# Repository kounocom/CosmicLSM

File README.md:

# CosmicLSM - An ESP32-C3 based custom SlimeVR PCB

## Notes:

 - Currently untested!
 - Designed for handsoldering, BOM contains parts that are "extended" on JLC, or straight up not present
 - CPL file not tested at all
 - See "Outputs/" for production files
 - IMUs that are compatible :
 - - BMI160
 - - BMI270
 - - BMI323(?)
 - - LSM6DSV
 - - LSM6DSV16X
 - - ICM-40608
 - - Potentially more, but there will be no firmware support, even for some of the ones listed above
 - Special thanks to Gorbit99 and wigwagwent for their help with making this <3

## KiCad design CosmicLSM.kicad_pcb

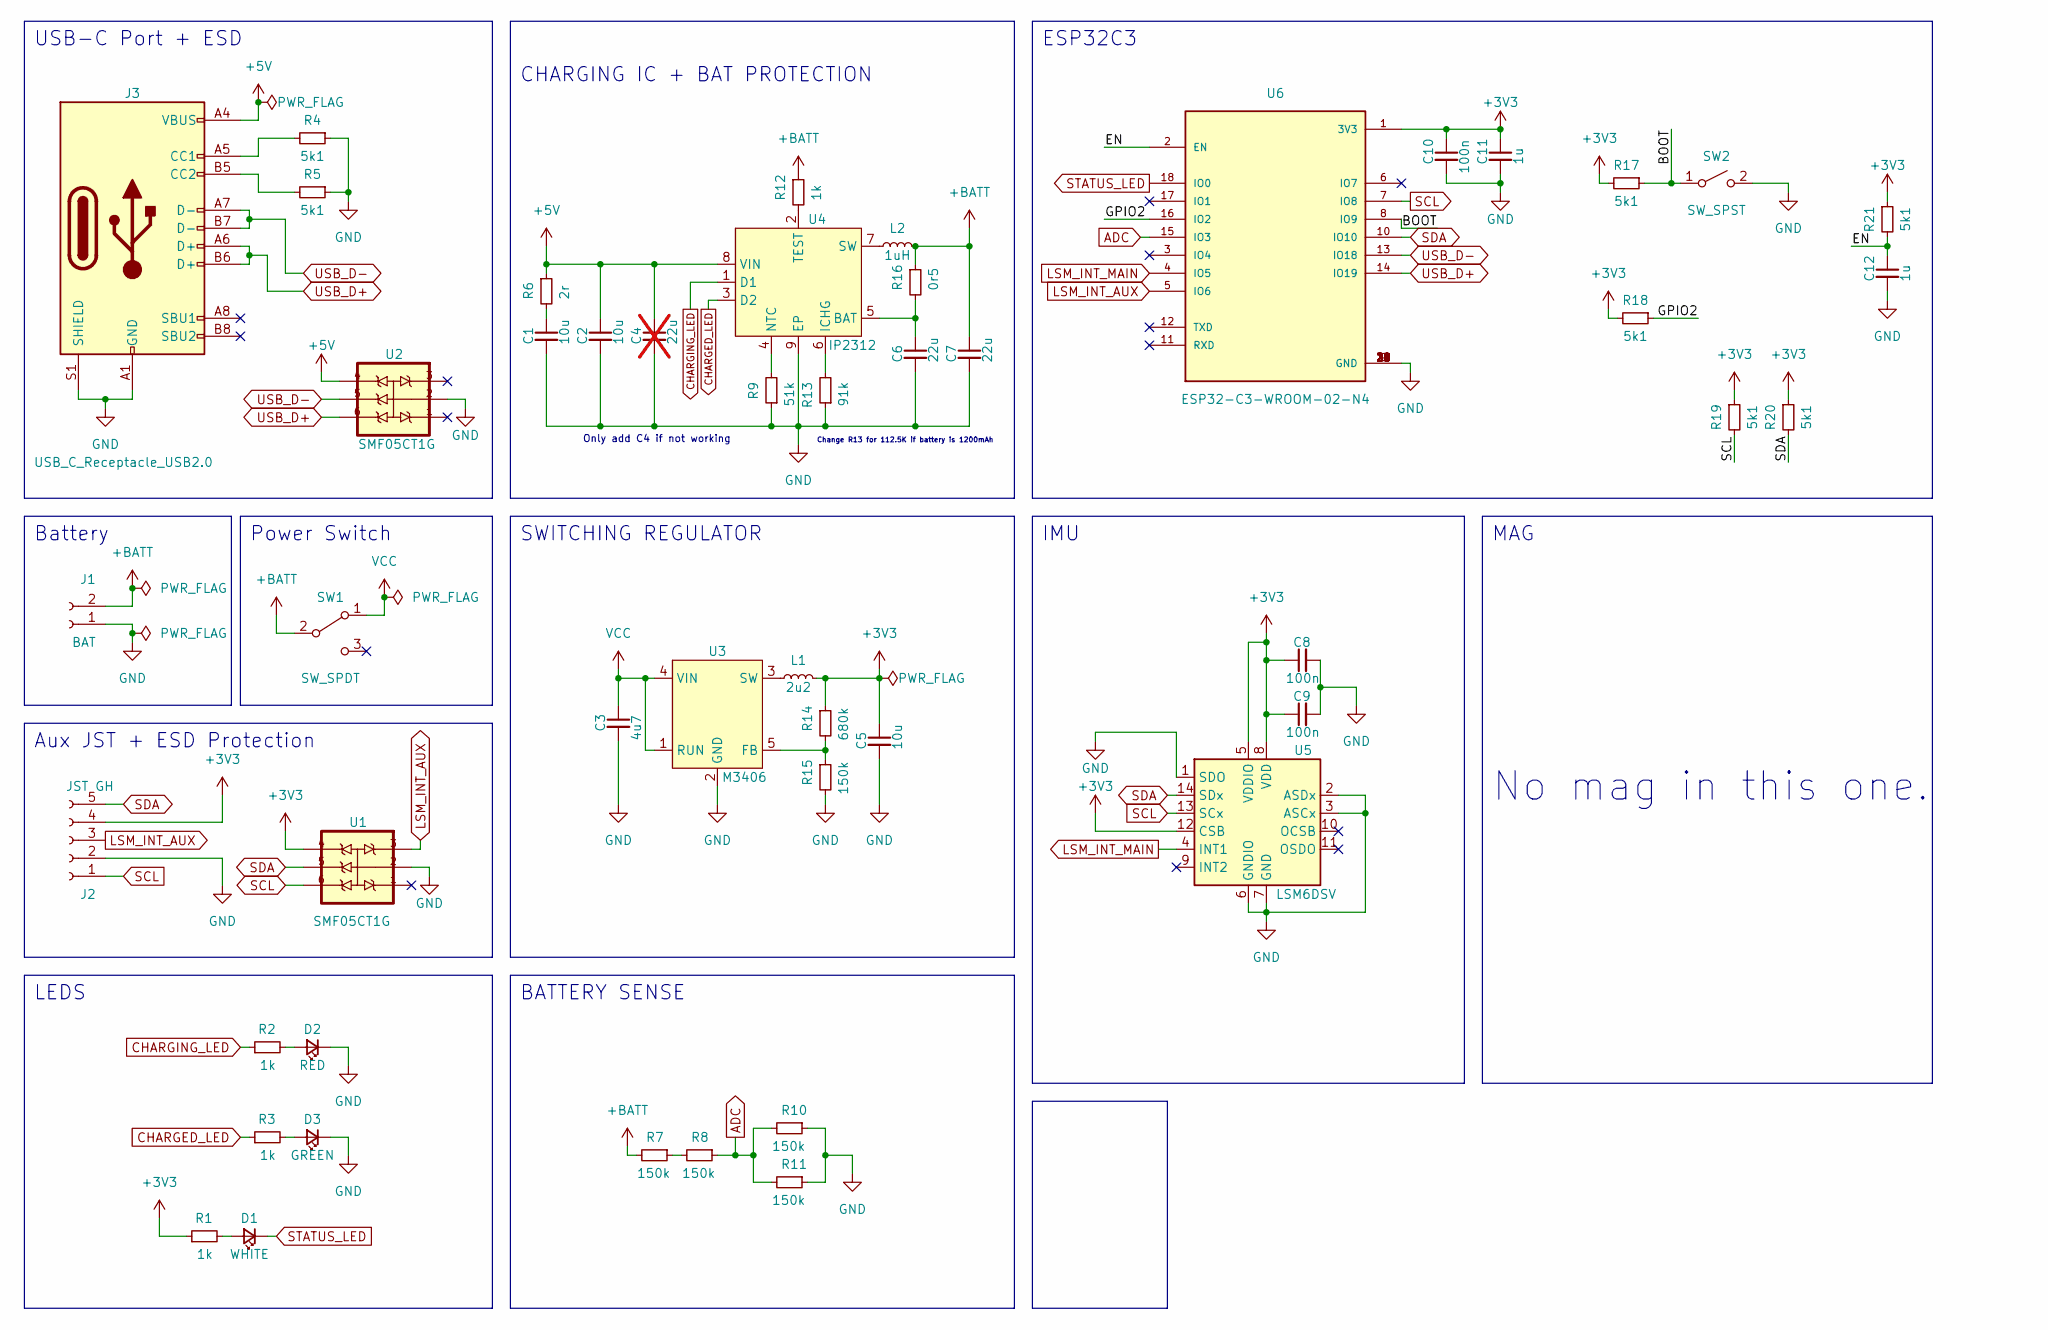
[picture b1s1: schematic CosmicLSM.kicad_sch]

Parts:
C1, C2, C5: 10u; C_0603_1608Metric_Pad1.08x0.95mm_HandSolder
C3: 4u7; C_0603_1608Metric_Pad1.08x0.95mm_HandSolder
C4: 22u; C_0603_1608Metric_Pad1.08x0.95mm_HandSolder; not fitted
C6, C7: 22u; C_0603_1608Metric_Pad1.08x0.95mm_HandSolder
C8, C9, C10: 100n; C_0603_1608Metric_Pad1.08x0.95mm_HandSolder
C11, C12: 1u; C_0603_1608Metric_Pad1.08x0.95mm_HandSolder
D1: WHITE; LED_0603_1608Metric_Pad1.05x0.95mm_HandSolder
D2: RED; LED_0603_1608Metric_Pad1.05x0.95mm_HandSolder
D3: GREEN; LED_0603_1608Metric_Pad1.05x0.95mm_HandSolder
J1: BAT; JST_PH_S2B-PH-SM4-TB_1x02-1MP_P2.00mm_Horizontal
J2: JST GH; JST_GH_SM05B-GHS-TB_1x05-1MP_P1.25mm_Horizontal
J3: USB_C_Receptacle_USB2.0; USB_C_Receptacle_XKB_U262-16XN-4BVC11
L1: 2u2; L_0603_1608Metric_Pad1.05x0.95mm_HandSolder
L2: 1uH; L_0805_2012Metric_Pad1.15x1.40mm_HandSolder
R1, R2, R3, R12: 1k; R_0603_1608Metric_Pad0.98x0.95mm_HandSolder
R4, R5, R17, R18, R19, R20, R21: 5k1; R_0603_1608Metric_Pad0.98x0.95mm_HandSolder
R6: 2r; R_0603_1608Metric_Pad0.98x0.95mm_HandSolder
R7, R8, R10, R11, R15: 150k; R_0603_1608Metric_Pad0.98x0.95mm_HandSolder
R9: 51k; R_0603_1608Metric_Pad0.98x0.95mm_HandSolder
R13: 91k; R_0603_1608Metric_Pad0.98x0.95mm_HandSolder
R14: 680k; R_0603_1608Metric_Pad0.98x0.95mm_HandSolder
R16: 0r5; R_0603_1608Metric_Pad0.98x0.95mm_HandSolder
SW1: SW_SPDT; SW_SPDT_PCM12
SW2: SW_SPST; SW_SPST_B3U-1000P
U1, U2: SMF05CT1G; SOT-363_SC-70-6
U3: M3406; SOT-23-5; LCSC C83224
U4: IP2312; HSOP-8-1EP_3.9x4.9mm_P1.27mm_EP2.41x3.1mm
U5: LSM6DSV; Bosch_LGA-14_3x2.5mm_P0.5mm
U6: ESP32-C3-WROOM-02-N4; MODULE_ESP32-C3-WROOM-02-H4

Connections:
+3V3: C5.1, C8.1, C9.1, C10.1, C11.1, J2.4, L1.2, R1.1, R14.1, R17.2, R18.2, R19.1, R20.1, R21.1, U1.4, U5.5 (VDDIO), U5.8 (VDD), U5.12 (CSB), U6.1 (3V3)
+5V: C2.1, C4.1, J3.A4 (VBUS), J3.A9 (VBUS), J3.B4 (VBUS), J3.B9 (VBUS), R6.1, U2.4, U4.8 (VIN)
+BATT: C7.1, J1.2 (Pin_1), L2.2, R7.2, R12.1, R16.1, SW1.2 (B)
/BOOT: R17.1, SW2.1 (A), U6.8 (IO9)
/EN: C12.1, R21.2, U6.2 (EN)
/GPIO2: R18.1, U6.16 (IO2)
ADC: R8.1, R10.2, R11.2, U6.15 (IO3)
CHARGED_LED: R3.1, U4.3 (D2)
CHARGING_LED: R2.1, U4.1 (D1)
GND: C1.2, C2.2, C3.2, C4.2, C5.2, C6.2, C7.2, C8.2, C9.2, C10.2, C11.2, C12.2, D2.1 (K), D3.1 (K), J1.1 (Pin_2), J2.2, J3.A1 (GND), J3.A12 (GND), J3.B1 (GND), J3.B12 (GND), J3.S1 (SHIELD), R4.1, R5.1, R9.1, R10.1, R11.1, R13.1, R15.2, SW2.2 (B), U1.2, U2.2, U3.2 (GND), U4.9 (EP), U5.1 (SDO), U5.2 (ASDx), U5.3 (ASCx), U5.6 (GNDIO), U5.7 (GND), U6.9 (GND), U6.19 (GND), U6.20 (GND), U6.21 (GND), U6.22 (GND), U6.23 (GND), U6.24 (GND), U6.25 (GND), U6.26 (GND), U6.27 (GND), U6.28 (GND), U6.29 (GND), U6.30 (GND), U6.31 (GND), U6.32 (GND), U6.33 (GND), U6.34 (GND), U6.35 (GND), U6.36 (GND), U6.37 (GND), U6.38 (GND), U6.39 (GND)
LSM_INT_AUX: J2.3, U1.3, U6.5 (IO6)
LSM_INT_MAIN: U5.4 (INT1), U6.4 (IO5)
unnamed: C1.1, R6.2
unnamed: D1.2 (A), R1.2
unnamed: D2.2 (A), R2.2
unnamed: D3.2 (A), R3.2
unnamed: J3.A5 (CC1), R4.2
unnamed: J3.B5 (CC2), R5.2
unnamed: R7.1, R8.2
unnamed: R14.2, R15.1, U3.5 (FB)
unnamed: L1.1, U3.3 (SW)
unnamed: C6.1, R16.2, U4.5 (BAT)
unnamed: R13.2, U4.6 (ICHG)
unnamed: R9.2, U4.4 (NTC)
unnamed: L2.1, U4.7 (SW)
unnamed: R12.2, U4.2 (TEST)
SCL: J2.1, R19.2, U1.6, U5.13 (SCx), U6.7 (IO8)
SDA: J2.5, R20.2, U1.5, U5.14 (SDx), U6.10 (IO10)
STATUS_LED: D1.1 (K), U6.18 (IO0)
USB_D+: J3.A6 (D+), J3.B6 (D+), U2.6, U6.14 (IO19)
USB_D-: J3.A7 (D-), J3.B7 (D-), U2.5, U6.13 (IO18)
VCC: C3.1, SW1.1 (A), U3.1 (RUN), U3.4 (VIN)

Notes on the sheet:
Battery
Only add C4 if not working
SWITCHING REGULATOR
No mag in this one.
ESP32C3
MAG
USB-C Port + ESD
IMU
Aux JST + ESD Protection
BATTERY SENSE
Change R13 for 112.5K if battery is 1200mAh
Power Switch
CHARGING IC + BAT PROTECTION
LEDS

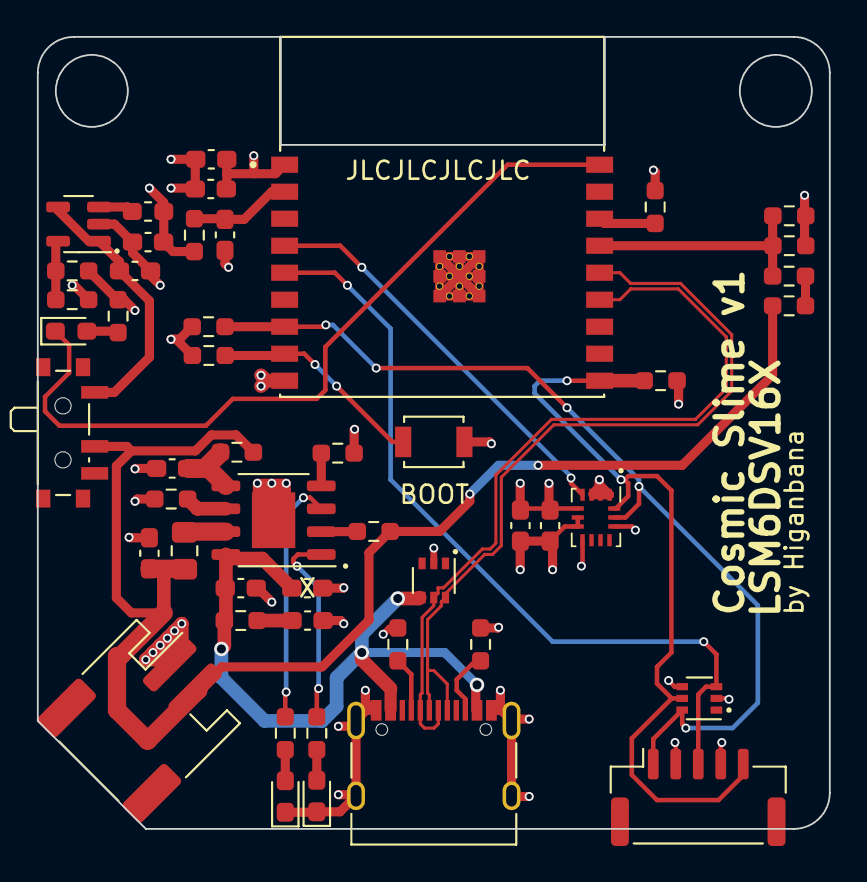
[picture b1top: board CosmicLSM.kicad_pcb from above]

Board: 4 copper layers, 44.0 x 44.0 mm, 49 parts (0 on the bottom side), 32 nets.

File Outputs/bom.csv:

Designator,Footprint,Quantity,Value,LCSC Part #,
"C1, C2, C5",603,3,10u,C1691,
"C10, C8, C9",603,3,100n,C1591,
"C11, C12",603,2,1u,C1592,
C3,603,1,4u7,C1705,
C4,603,1,22u,IGNORE,
"C6, C7",603,3,22u,C59461,
D1,603,1,WHITE,C84265,
D2,603,1,RED,C264473,
D3,603,1,GREEN,C965804,
J1,JST_PH_S2B-PH-SM4-TB_1x02-1MP_P2.00mm_Horizontal,1,BAT,C295747,
J2,JST_GH_SM05B-GHS-TB_1x05-1MP_P1.25mm_Horizontal,1,JST GH,C189896,
J3,USB_C_Receptacle_XKB_U262-16XN-4BVC11,1,USB_C_Receptacle_USB2.0,C2765186,
L1,603,1,2u2,C285966,
L2,805,1,1uH,C433051,
"R1, R12, R2, R3",603,4,1k,C21190,
"R10, R11, R15, R7, R8",603,5,150k,C22807,
R13,603,1,112.5k,C25808,
R14,603,1,680k,C25822,
R16,603,1,0r5,C45312,
"R17, R18, R19, R20, R21, R4, R5",603,7,5k1,C23186,
R6,603,1,2r,C22977,
R9,603,1,51k,C23196,
SW1,SW_SPDT_PCM12,1,SW_SPDT,C109335,
SW2,SW_SPST_B3U-1000P,1,SW_SPST,C231329,
"U1, U2",SOT-363_SC-70-6,2,SMF05CT1G,C15879,
U3,SOT-23-5,1,M3406,C83224,
U4,HSOP-8-1EP_3.9x4.9mm_P1.27mm_EP2.41x3.1mm,1,IP2312,C605433,
U5,Bosch_LGA-14_3x2.5mm_P0.5mm,1,LSM6DSV,IGNORE,
U6,MODULE_ESP32-C3-WROOM-02-H4,1,ESP32-C3-WROOM-02-N4,C2934560,

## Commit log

2023-09-06 init
2023-09-06 oops it had the old schematic image ehe
2023-09-07 added readme and license

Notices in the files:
CosmicLSM.kicad_sch:
Licensed under CERN-OHL-P 2
